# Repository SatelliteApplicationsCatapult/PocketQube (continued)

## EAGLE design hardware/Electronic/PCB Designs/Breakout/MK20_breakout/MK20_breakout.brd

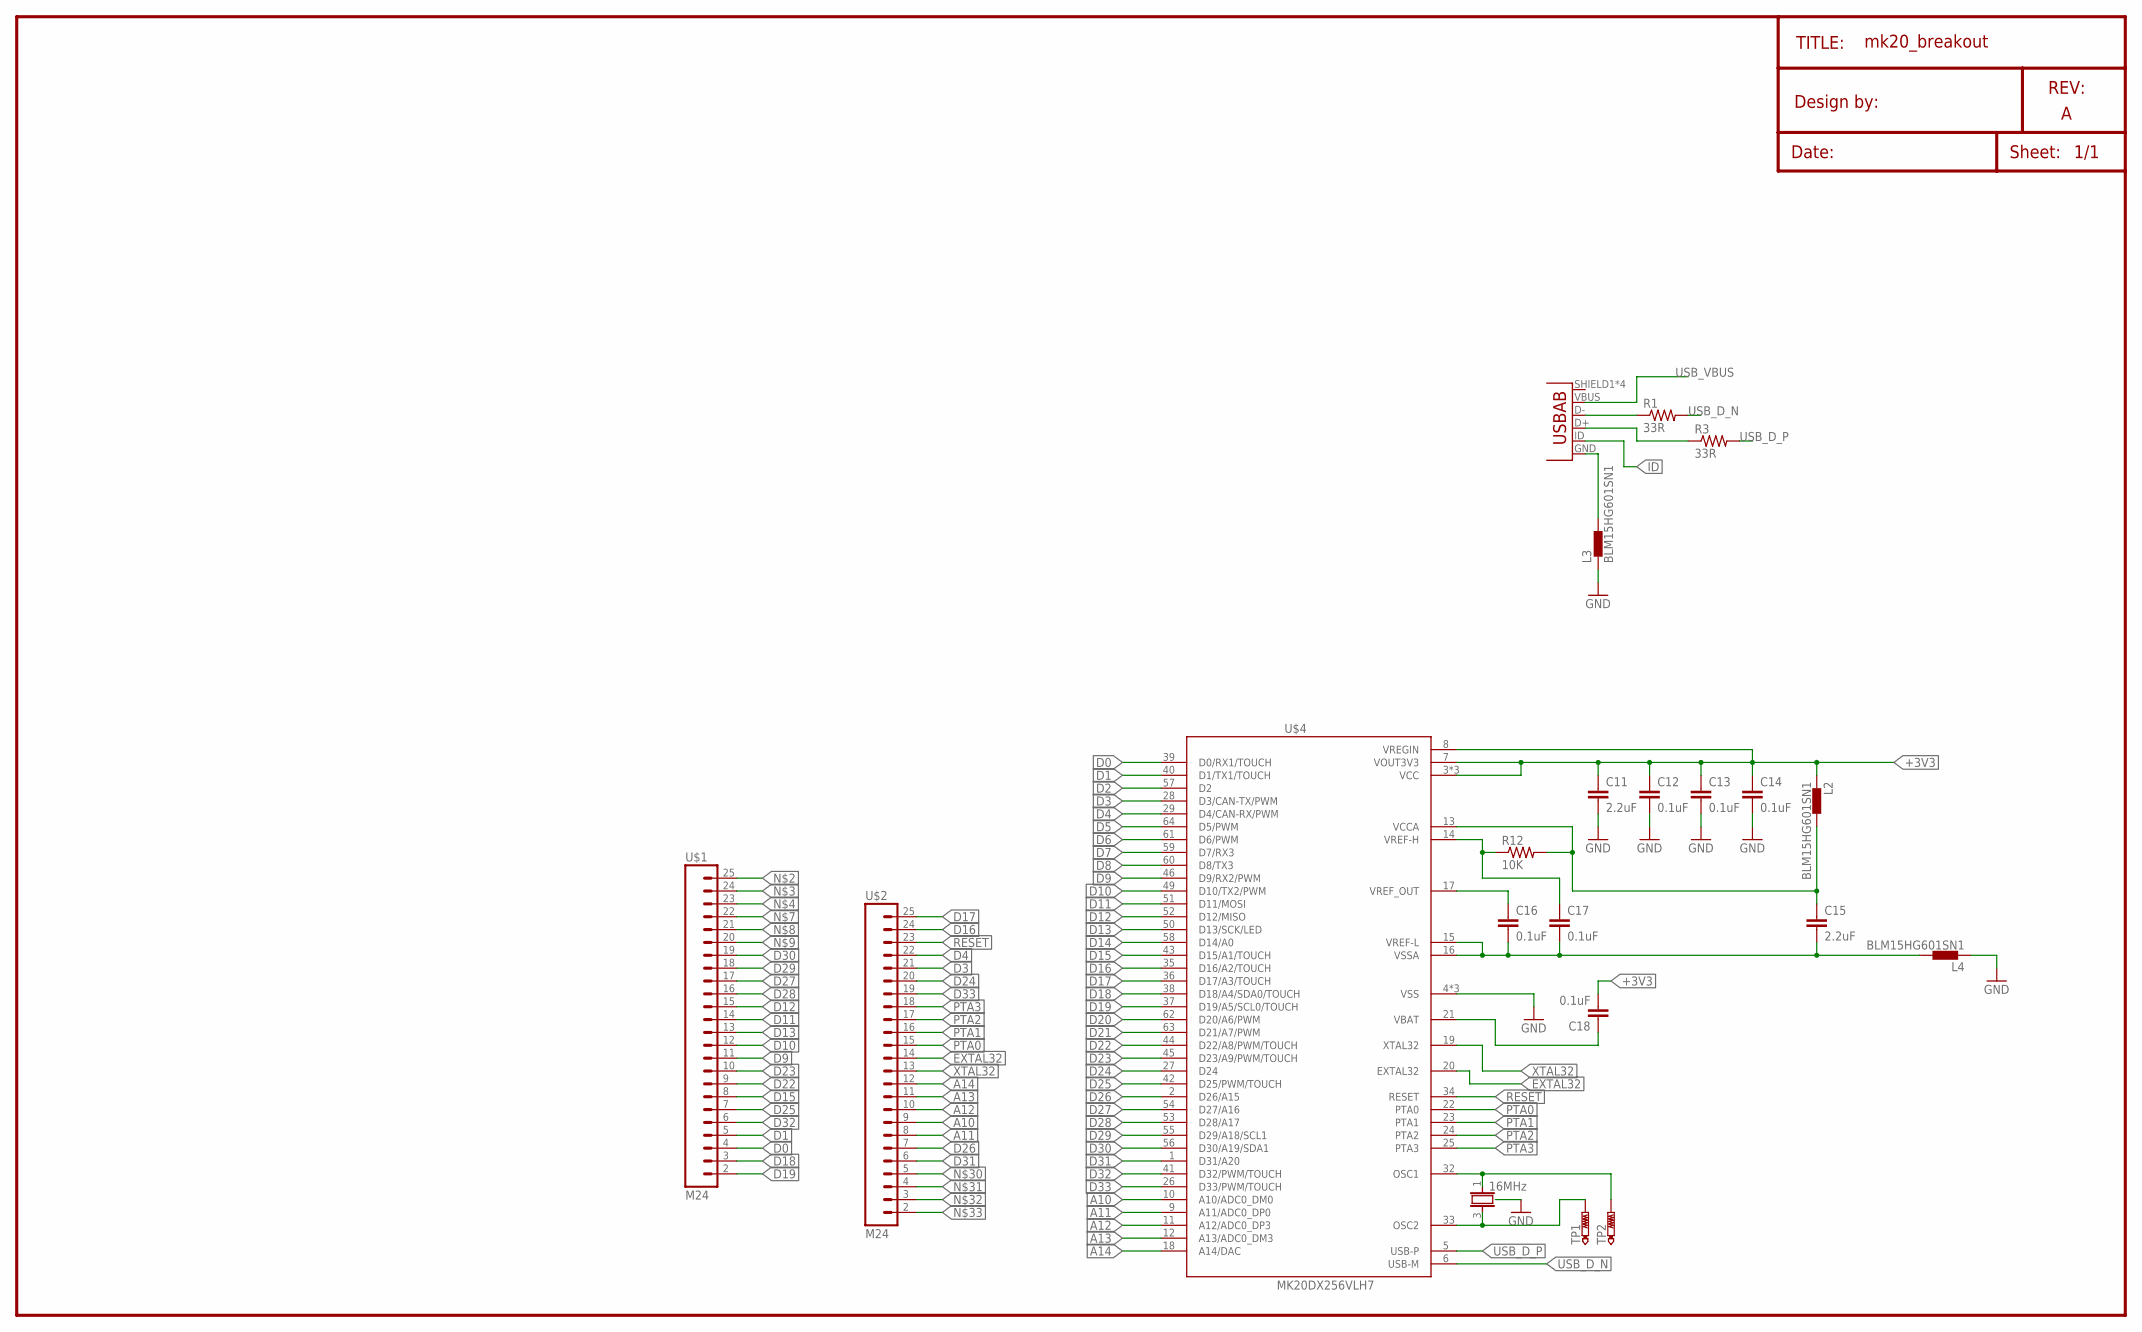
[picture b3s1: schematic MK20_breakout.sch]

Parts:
C11, C15: 2.2uF; C0603
C12, C13, C14, C16, C17: 0.1uF; C0402
C18: 0.1uF; C0603
JP1: MOLEX 105017-0001; USB-AB-MICRO-SMD
L2, L3, L4: BLM15HG601SN1; 0402
NDK_NX3225SA: 16MHz; 4SMD_DFN_LCC
R1, R3: 33R; 0603-RES
R12: 10K; 0402-RES
TP1, TP2: PTR1TP06R; TP06R
U$1, U$2: M24; 1X24
U$4: MK20DX256VLH7; QFP50P1200X1200X160-64N

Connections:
+3V3: C11.1, C12.1, C13.1, C14.1, C18.2, L2.1, U$4.3 (VCC), U$4.7 (VOUT3V3), U$4.8 (VREGIN), U$4.30 (VCC), U$4.48 (VCC)
A10: U$2.9, U$4.10 (A10/ADC0_DM0)
A11: U$2.8, U$4.9 (A11/ADC0_DP0)
A12: U$2.10, U$4.11 (A12/ADC0_DP3)
A13: U$2.11, U$4.12 (A13/ADC0_DM3)
A14: U$2.12, U$4.18 (A14/DAC)
D0: U$1.4, U$4.39 (D0/RX1/TOUCH)
D1: U$1.5, U$4.40 (D1/TX1/TOUCH)
D2: U$4.57 (D2)
D3: U$2.21, U$4.28 (D3/CAN-TX/PWM)
D4: U$2.22, U$4.29 (D4/CAN-RX/PWM)
D5: U$4.64 (D5/PWM)
D6: U$4.61 (D6/PWM)
D7: U$4.59 (D7/RX3)
D8: U$4.60 (D8/TX3)
D9: U$1.11, U$4.46 (D9/RX2/PWM)
D10: U$1.12, U$4.49 (D10/TX2/PWM)
D11: U$1.14, U$4.51 (D11/MOSI)
D12: U$1.15, U$4.52 (D12/MISO)
D13: U$1.13, U$4.50 (D13/SCK/LED)
D14: U$4.58 (D14/A0)
D15: U$1.8, U$4.43 (D15/A1/TOUCH)
D16: U$2.24, U$4.35 (D16/A2/TOUCH)
D17: U$2.25, U$4.36 (D17/A3/TOUCH)
D18: U$1.3, U$4.38 (D18/A4/SDA0/TOUCH)
D19: U$1.2, U$4.37 (D19/A5/SCL0/TOUCH)
D20: U$4.62 (D20/A6/PWM)
D21: U$4.63 (D21/A7/PWM)
D22: U$1.9, U$4.44 (D22/A8/PWM/TOUCH)
D23: U$1.10, U$4.45 (D23/A9/PWM/TOUCH)
D24: U$2.20, U$4.27 (D24)
D25: U$1.7, U$4.42 (D25/PWM/TOUCH)
D26: U$2.7, U$4.2 (D26/A15)
D27: U$1.17, U$4.54 (D27/A16)
D28: U$1.16, U$4.53 (D28/A17)
D29: U$1.18, U$4.55 (D29/A18/SCL1)
D30: U$1.19, U$4.56 (D30/A19/SDA1)
D31: U$2.6, U$4.1 (D31/A20)
D32: U$1.6, U$4.41 (D32/PWM/TOUCH)
D33: U$2.19, U$4.26 (D33/PWM/TOUCH)
EXTAL32: U$2.14, U$4.20 (EXTAL32)
GND: C11.2, C12.2, C13.2, C14.2, L3.1, L4.1, NDK_NX3225SA.GND, NDK_NX3225SA.GND@1 (GND), NDK_NX3225SA.GND@2 (GND), U$4.4 (VSS), U$4.31 (VSS), U$4.47 (VSS)
ID: JP1.ID (USBID)
unnamed: NDK_NX3225SA.1, TP2.TP, U$4.32 (OSC1)
unnamed: JP1.D+, R3.1
unnamed: JP1.D-, R1.1
unnamed: NDK_NX3225SA.3, TP1.TP, U$4.33 (OSC2)
unnamed: C15.1, L2.2, R12.2, U$4.13 (VCCA)
unnamed: C17.1, R12.1, U$4.14 (VREF-H)
unnamed: C15.2, C16.2, C17.2, L4.2, U$4.15 (VREF-L), U$4.16 (VSSA)
unnamed: C16.1, U$4.17 (VREF_OUT)
unnamed: C18.1, U$4.21 (VBAT)
unnamed: JP1.GND, L3.2
PTA0: U$2.15, U$4.22 (PTA0)
PTA1: U$2.16, U$4.23 (PTA1)
PTA2: U$2.17, U$4.24 (PTA2)
PTA3: U$2.18, U$4.25 (PTA3)
RESET: U$2.23, U$4.34 (RESET)
USB_D_N: R1.2, U$4.6 (USB-M)
USB_D_P: R3.2, U$4.5 (USB-P)
USB_VBUS: JP1.VBUS
XTAL32: U$2.13, U$4.19 (XTAL32)

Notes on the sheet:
TITLE:
Date:
REV:
Sheet:
Design by:

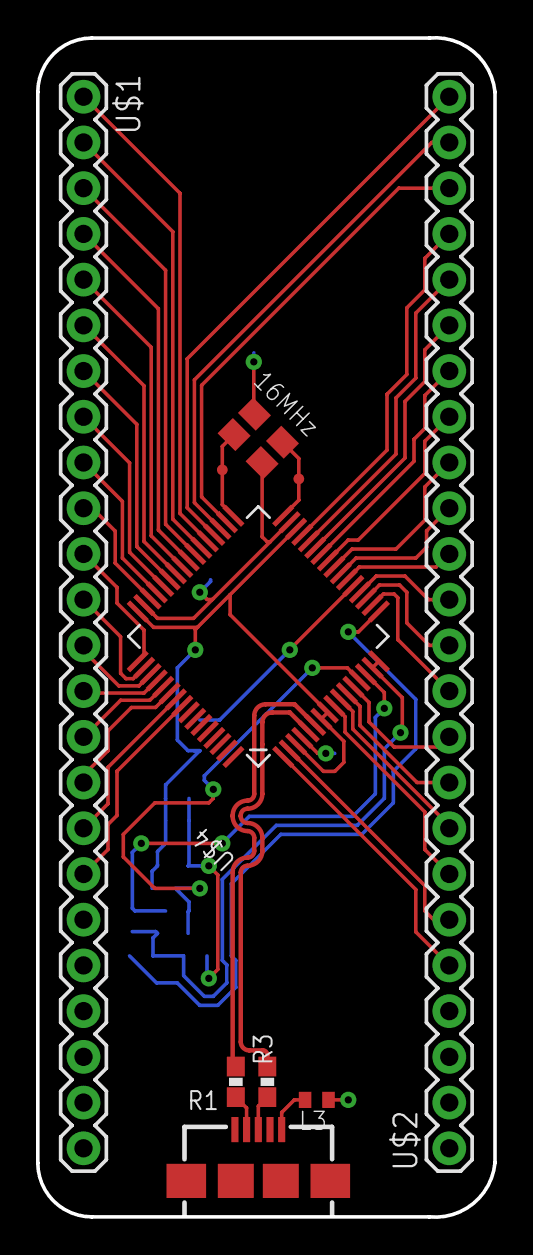
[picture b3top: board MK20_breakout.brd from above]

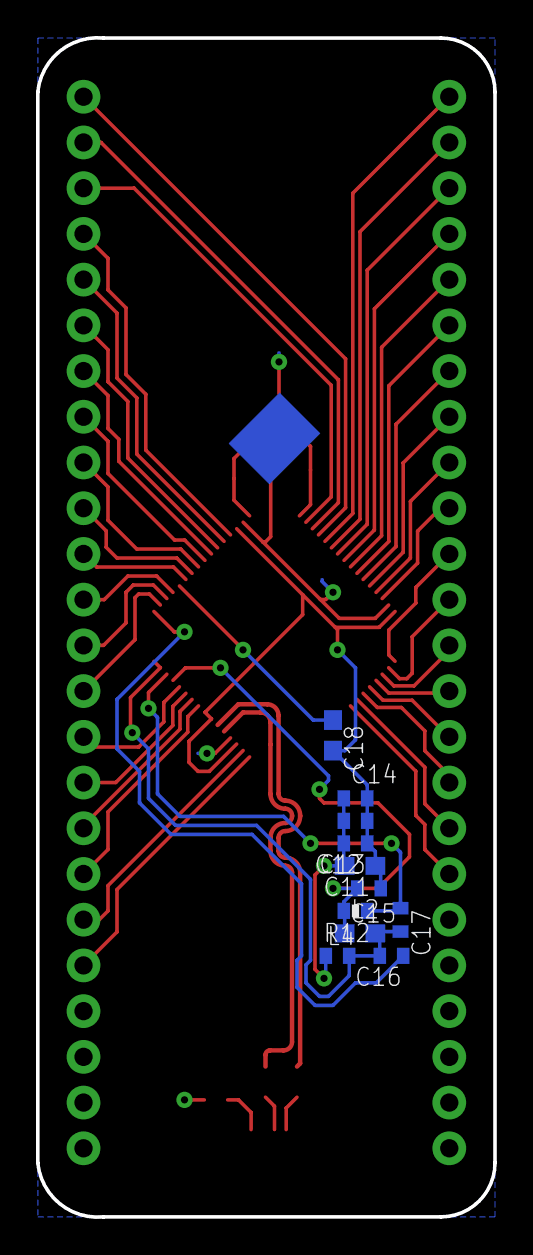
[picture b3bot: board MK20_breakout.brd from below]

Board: 2 copper layers, 25.4 x 65.5 mm, 21 parts (11 on the bottom side), 52 nets.

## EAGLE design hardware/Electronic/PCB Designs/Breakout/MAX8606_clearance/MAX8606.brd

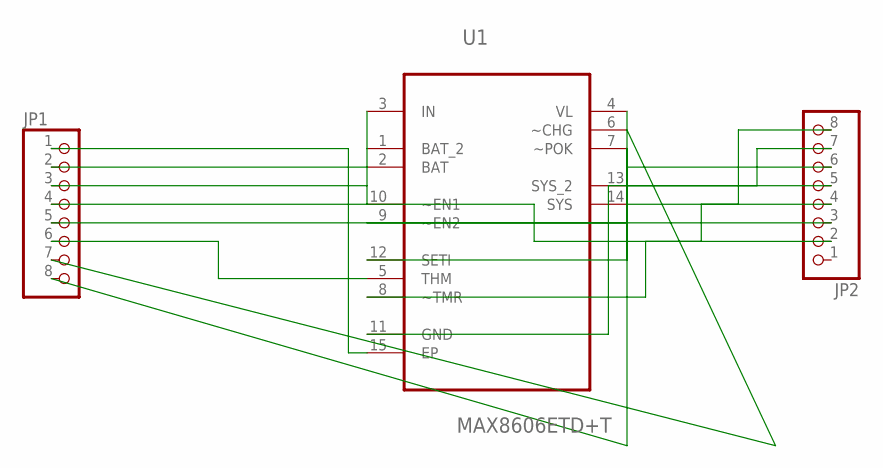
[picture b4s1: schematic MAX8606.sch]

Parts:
JP1, JP2: PINHD-1X8CLEANBIG; 1X08-CLEANBIG
U1: MAX8606ETD+T; DFN300X300X80-15N

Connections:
GND: JP1.1, JP2.5, U1.11 (GND), U1.15 (EP)
unnamed: JP2.8, U1.14 (SYS)
unnamed: JP2.7, U1.13 (SYS_2)
unnamed: JP2.6, U1.12 (SETI)
unnamed: JP2.4, U1.10 (~EN1)
unnamed: JP2.3, U1.9 (~EN2)
unnamed: JP2.2, U1.8 (~TMR)
unnamed: JP1.8, U1.7 (~POK)
unnamed: JP1.7, U1.6 (~CHG)
unnamed: JP1.5, U1.4 (VL)
unnamed: JP1.2, JP1.3, JP1.4, U1.3 (IN)
unnamed: JP1.6, U1.5 (THM)

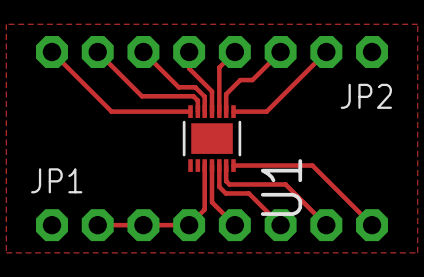
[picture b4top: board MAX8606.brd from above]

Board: 2 copper layers, 3 parts (0 on the bottom side), 12 nets.

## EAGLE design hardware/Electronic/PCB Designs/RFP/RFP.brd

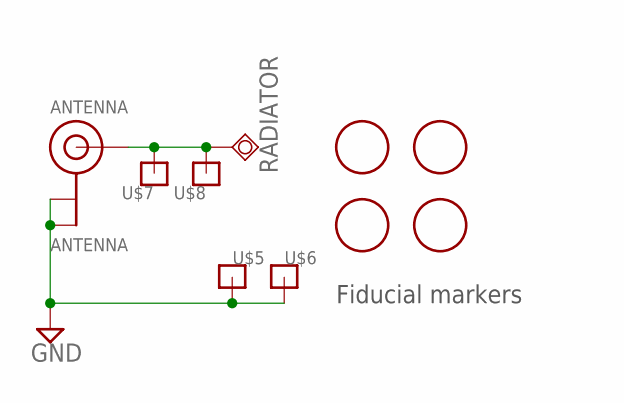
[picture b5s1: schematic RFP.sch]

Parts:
ANTENNA: ANTENNA; U.FL
FD1, FD2, FD3, FD4: FIDUCIAL; FIDUCIAL_1MM
RADIATOR: TPSQTP20SQ; TP20SQ
U$5, U$6, U$7, U$8: 2MMPILLAR

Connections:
GND: ANTENNA.1 (GND), ANTENNA.2 (GND), U$5.P$1, U$6.P$1
SIGNAL: ANTENNA.3 (SIGNAL), RADIATOR.TP, U$7.P$1, U$8.P$1

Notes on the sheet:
Fiducial markers

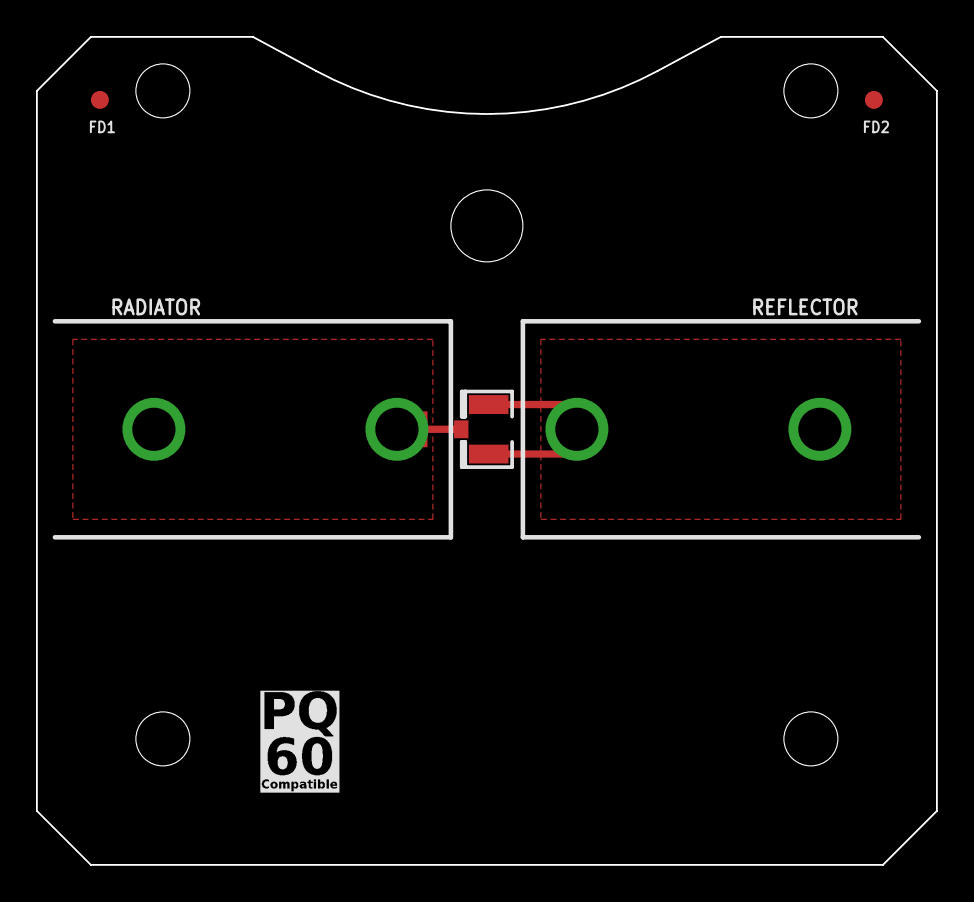
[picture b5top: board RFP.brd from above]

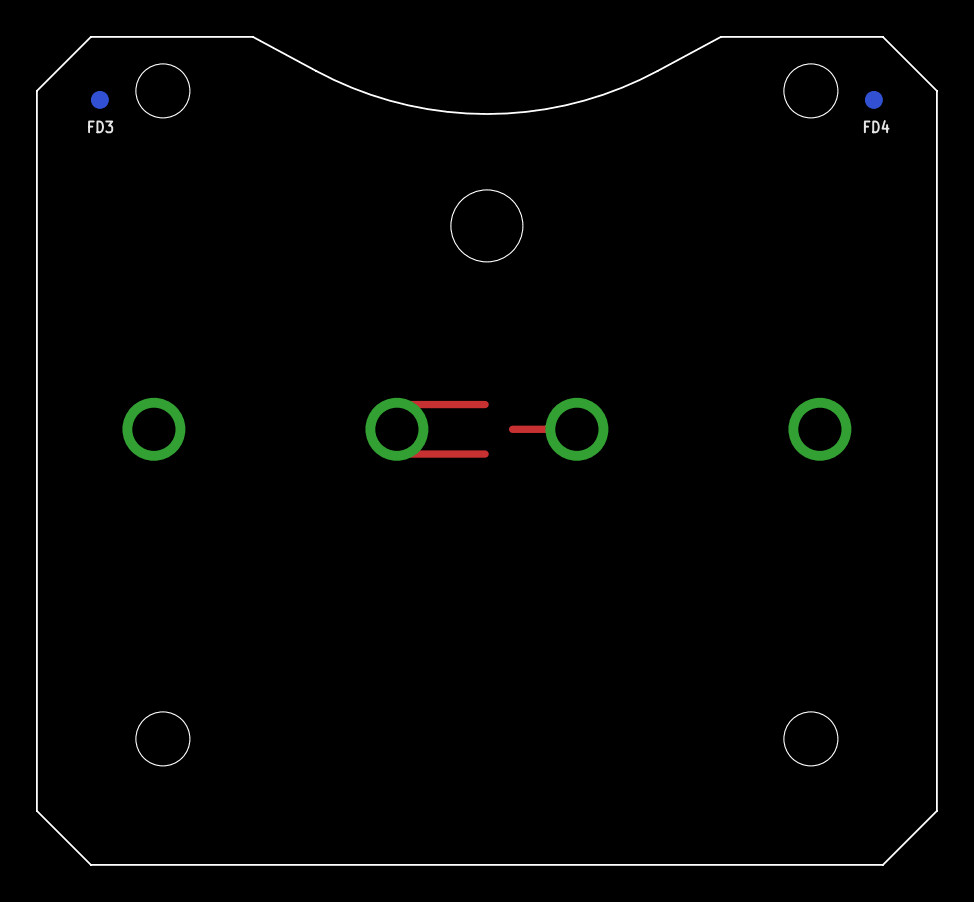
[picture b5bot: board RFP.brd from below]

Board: 2 copper layers, 50.0 x 46.0 mm, 13 parts (2 on the bottom side), 2 nets.

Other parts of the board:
U$9: SA_LOGO_SMALL
U$10: PQ60_CMP
U$12: UBO_LOGO_LARGE

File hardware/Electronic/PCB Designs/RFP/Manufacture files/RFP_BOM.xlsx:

Qty | Value | Device | Package | Parts | Description | Supplier | Order number | Notes
4 | 2MMPILLAR | 2MMPILLAR | 2MMPILLAR | U$5, U$6, U$7, U$8 |  |  |  | Do not populate
1 | ANTENNA | ANTENNA_U.FL | U.FL | ANTENNA | U.FL Antenna Connector | Farnell | 1688077 | Or compatible alternative
4 | FIDUCIAL | FIDUCIAL | FIDUCIAL_1MM | FD1, FD2, FD3, FD4 | For use by pick and place machines to calibrate the vision/machine, 1mm |  |  | Do not populate
1 | TPSQTP20SQ | TPSQTP20SQ | TP20SQ | RADIATOR | Test pad |  |  | Do not populate

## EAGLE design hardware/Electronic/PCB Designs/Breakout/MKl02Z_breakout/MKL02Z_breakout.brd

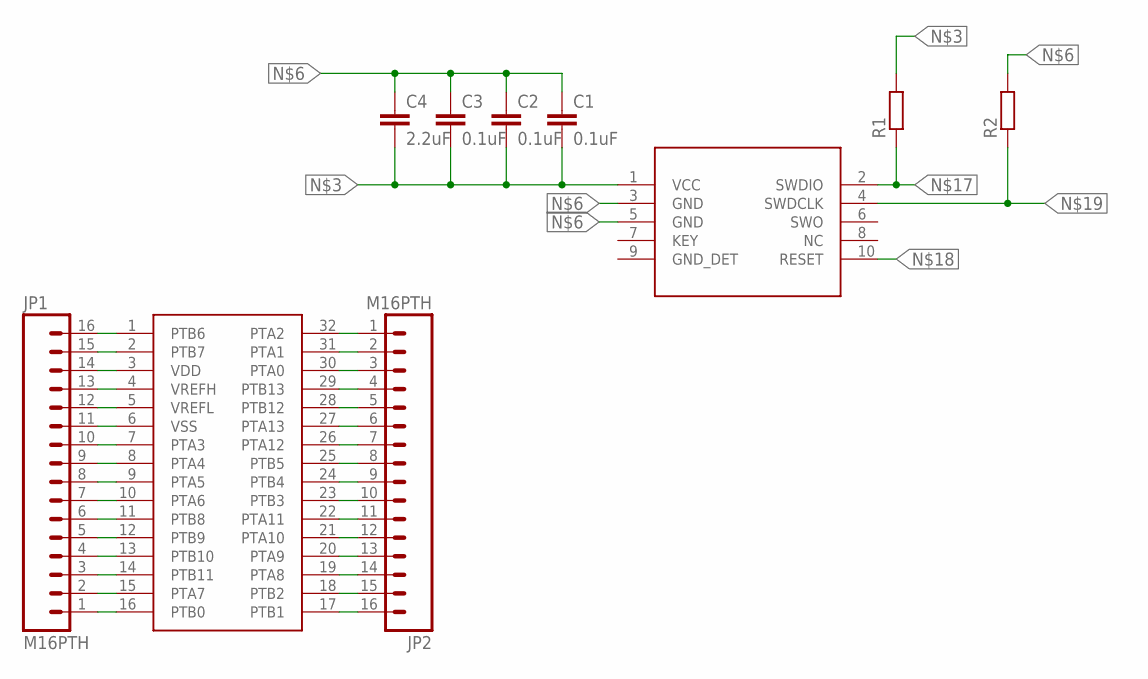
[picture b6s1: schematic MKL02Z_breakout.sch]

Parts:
C1, C2, C3: 0.1uF; C0603
C4: 2.2uF; C0603
JP1, JP2: M16PTH; 1X16
R1, R2: R-EU_R0603; R0603
U$1: MKL02Z16VFM4
U$2: SWD_10_PIN

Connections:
unnamed: JP1.16, U$1.1 (PTB6)
unnamed: JP1.15, U$1.2 (PTB7)
unnamed: C1.2, C2.2, C3.2, C4.2, JP1.14, R1.2, U$1.3 (VDD), U$2.1 (VCC)
unnamed: JP1.13, U$1.4 (VREFH)
unnamed: JP1.12, U$1.5 (VREFL)
unnamed: C1.1, C2.1, C3.1, C4.1, JP1.11, R2.2, U$1.6 (VSS), U$2.3 (GND), U$2.5 (GND)
unnamed: JP1.10, U$1.7 (PTA3)
unnamed: JP1.9, U$1.8 (PTA4)
unnamed: JP1.8, U$1.9 (PTA5)
unnamed: JP1.7, U$1.10 (PTA6)
unnamed: JP1.6, U$1.11 (PTB8)
unnamed: JP1.5, U$1.12 (PTB9)
unnamed: JP1.4, U$1.13 (PTB10)
unnamed: JP1.3, U$1.14 (PTB11)
unnamed: JP1.2, U$1.15 (PTA7)
unnamed: JP1.1, U$1.16 (PTB0)
unnamed: JP2.1, R1.1, U$1.32 (PTA2), U$2.2 (SWDIO)
unnamed: JP2.2, U$1.31 (PTA1), U$2.10 (RESET)
unnamed: JP2.3, R2.1, U$1.30 (PTA0), U$2.4 (SWDCLK)
unnamed: JP2.4, U$1.29 (PTB13)
unnamed: JP2.5, U$1.28 (PTB12)
unnamed: JP2.6, U$1.27 (PTA13)
unnamed: JP2.7, U$1.26 (PTA12)
unnamed: JP2.8, U$1.25 (PTB5)
unnamed: JP2.9, U$1.24 (PTB4)
unnamed: JP2.10, U$1.23 (PTB3)
unnamed: JP2.11, U$1.22 (PTA11)
unnamed: JP2.12, U$1.21 (PTA10)
unnamed: JP2.13, U$1.20 (PTA9)
unnamed: JP2.14, U$1.19 (PTA8)
unnamed: JP2.15, U$1.18 (PTB2)
unnamed: JP2.16, U$1.17 (PTB1)

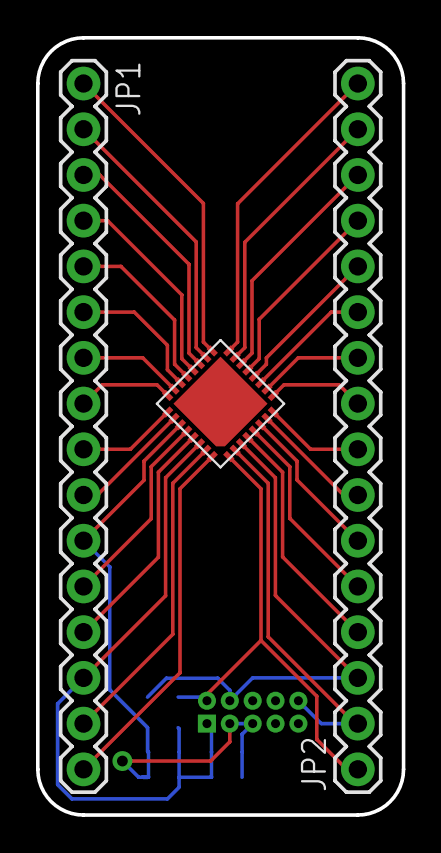
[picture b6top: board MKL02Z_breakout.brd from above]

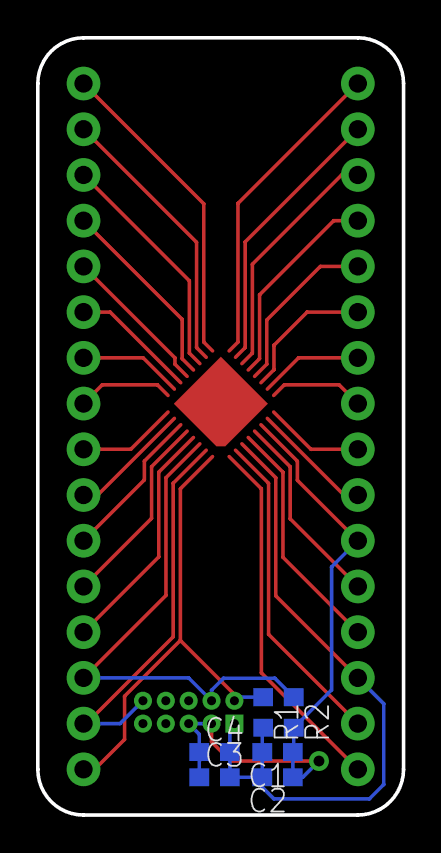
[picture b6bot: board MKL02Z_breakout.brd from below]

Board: 2 copper layers, 20.3 x 43.2 mm, 10 parts (6 on the bottom side), 32 nets.

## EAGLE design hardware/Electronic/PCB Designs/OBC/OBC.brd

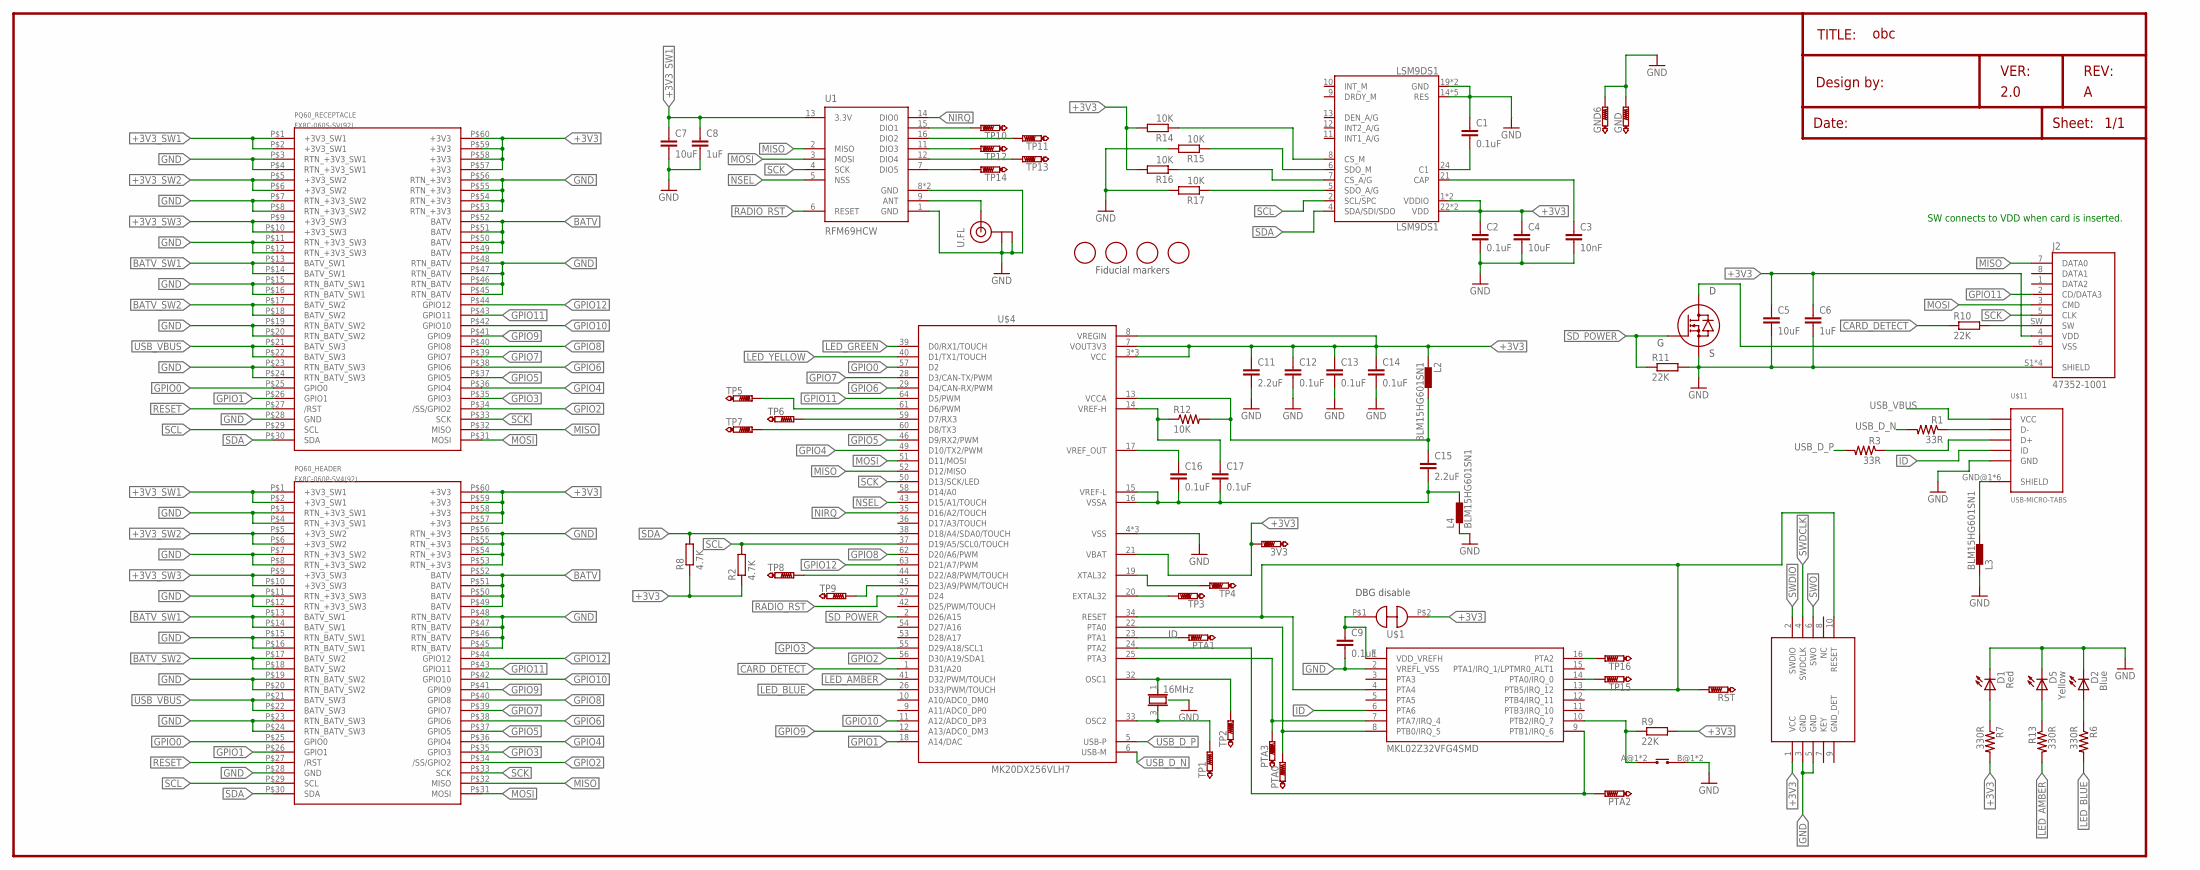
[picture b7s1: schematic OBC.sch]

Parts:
3V3: PTR1TP06R; TP06R
C1, C2, C9, C12, C13, C14, C16, C17: 0.1uF; C0402
C3: 10nF; C0402
C4, C5, C7: 10uF; C0805
C6, C8: 1uF; C0603
C11, C15: 2.2uF; C0603
D1: Red; CHIPLED_0603
D2: Blue; CHIPLED_0603
D5: Yellow; CHIPLED_0603
ERASE: EVPAF7B70
FD1, FD2, FD3, FD4: FIDUCIAL; FIDUCIAL_1MM
GND, GND6: PTR1TP06R; TP06R
J2: 47352-1001; MOLEX_47352-1001
L2, L3, L4: BLM15HG601SN1; 0402
LSM9DS1: LSM9DS1; LGA24-8X4
NDK_NX3225SA: 16MHz; 4SMD_DFN_LCC
PQ60_HEADER: FX8C-060P-SV4(92)
PQ60_RECEPTACLE: FX8C-060S-SV(92)
PTA0, PTA1, PTA2, PTA3: PTR1TP06R; TP06R
R1, R3: 33R; 0603-RES
R2, R8: 4.7K; R0402
R6, R7, R13: 330R; 0603-RES
R9, R10, R11: 22K; R0402
R12: 10K; 0402-RES
R14, R15, R16, R17: 10K; R0402
RST: PTR1TP06R; TP06R
SJ3: SJNC
TP1, TP2, TP3, TP4, TP5, TP6, TP7, TP8, TP9, TP10, TP11, TP12, TP13, TP14, TP15, TP16: PTR1TP06R; TP06R
U1: RFM69HCW; RFM69HCW-XXXS2
U$1: MKL02Z32VFG4SMD; QFN16
U$3: PMV40UN2; SOT23-3
U$4: MK20DX256VLH7; QFP50P1200X1200X160-64N
U$9: SWD_10_PIN
U$11: USB-MICRO-TABS
U.FL: U.FL

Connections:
+3V3: 3V3.TP, C2.1, C4.1, C5.1, C6.1, C11.1, C12.1, C13.1, C14.1, J2.4 (VDD), L2.1, LSM9DS1.1 (VDDIO), LSM9DS1.3 (VDDIO), LSM9DS1.22 (VDD), LSM9DS1.23 (VDD), PQ60_HEADER.P$57 (+3V3), PQ60_HEADER.P$58 (+3V3), PQ60_HEADER.P$59 (+3V3), PQ60_HEADER.P$60 (+3V3), PQ60_RECEPTACLE.P$57 (+3V3), PQ60_RECEPTACLE.P$58 (+3V3), PQ60_RECEPTACLE.P$59 (+3V3), PQ60_RECEPTACLE.P$60 (+3V3), R2.1, R7.2, R8.1, R9.2, R14.2, R16.2, SJ3.P$2, U$4.3 (VCC), U$4.7 (VOUT3V3), U$4.8 (VREGIN), U$4.21 (VBAT), U$4.30 (VCC), U$4.48 (VCC), U$9.1 (VCC)
+3V3_SW1: C7.1, C8.1, PQ60_HEADER.P$1 (+3V3_SW1), PQ60_HEADER.P$2 (+3V3_SW1), PQ60_RECEPTACLE.P$1 (+3V3_SW1), PQ60_RECEPTACLE.P$2 (+3V3_SW1), U1.13 (3.3V)
+3V3_SW2: PQ60_HEADER.P$5 (+3V3_SW2), PQ60_HEADER.P$6 (+3V3_SW2), PQ60_RECEPTACLE.P$5 (+3V3_SW2), PQ60_RECEPTACLE.P$6 (+3V3_SW2)
+3V3_SW3: PQ60_HEADER.P$9 (+3V3_SW3), PQ60_HEADER.P$10 (+3V3_SW3), PQ60_RECEPTACLE.P$9 (+3V3_SW3), PQ60_RECEPTACLE.P$10 (+3V3_SW3)
BATV: PQ60_HEADER.P$49 (BATV), PQ60_HEADER.P$50 (BATV), PQ60_HEADER.P$51 (BATV), PQ60_HEADER.P$52 (BATV), PQ60_RECEPTACLE.P$49 (BATV), PQ60_RECEPTACLE.P$50 (BATV), PQ60_RECEPTACLE.P$51 (BATV), PQ60_RECEPTACLE.P$52 (BATV)
BATV_SW1: PQ60_HEADER.P$13 (BATV_SW1), PQ60_HEADER.P$14 (BATV_SW1), PQ60_RECEPTACLE.P$13 (BATV_SW1), PQ60_RECEPTACLE.P$14 (BATV_SW1)
BATV_SW2: PQ60_HEADER.P$17 (BATV_SW2), PQ60_HEADER.P$18 (BATV_SW2), PQ60_RECEPTACLE.P$17 (BATV_SW2), PQ60_RECEPTACLE.P$18 (BATV_SW2)
CARD_DETECT: R10.1, U$4.1 (D31/A20)
GND: C1.1, C2.2, C3.2, C4.2, C5.2, C6.2, C7.2, C8.2, C9.2, C11.2, C12.2, C13.2, C14.2, D1.C, D2.C, D5.C, ERASE.B@1, ERASE.B@2, GND.TP, GND6.TP, J2.S1 (SHIELD), J2.S2 (SHIELD), J2.S3 (SHIELD), J2.S4 (SHIELD), L3.1, L4.1, LSM9DS1.14 (RES), LSM9DS1.15 (RES), LSM9DS1.16 (RES), LSM9DS1.17 (RES), LSM9DS1.18 (RES), LSM9DS1.19 (GND), LSM9DS1.20 (GND), NDK_NX3225SA.GND, NDK_NX3225SA.GND@1 (GND), NDK_NX3225SA.GND@2 (GND), PQ60_HEADER.P$3 (RTN_+3V3_SW1), PQ60_HEADER.P$4 (RTN_+3V3_SW1), PQ60_HEADER.P$7 (RTN_+3V3_SW2), PQ60_HEADER.P$8 (RTN_+3V3_SW2), PQ60_HEADER.P$11 (RTN_+3V3_SW3), PQ60_HEADER.P$12 (RTN_+3V3_SW3), PQ60_HEADER.P$15 (RTN_BATV_SW1), PQ60_HEADER.P$16 (RTN_BATV_SW1), PQ60_HEADER.P$19 (RTN_BATV_SW2), PQ60_HEADER.P$20 (RTN_BATV_SW2), PQ60_HEADER.P$23 (RTN_BATV_SW3), PQ60_HEADER.P$24 (RTN_BATV_SW3), PQ60_HEADER.P$28 (GND), PQ60_HEADER.P$45 (RTN_BATV), PQ60_HEADER.P$46 (RTN_BATV), PQ60_HEADER.P$47 (RTN_BATV), PQ60_HEADER.P$48 (RTN_BATV), PQ60_HEADER.P$53 (RTN_+3V3), PQ60_HEADER.P$54 (RTN_+3V3), PQ60_HEADER.P$55 (RTN_+3V3), PQ60_HEADER.P$56 (RTN_+3V3), PQ60_RECEPTACLE.P$3 (RTN_+3V3_SW1), PQ60_RECEPTACLE.P$4 (RTN_+3V3_SW1), PQ60_RECEPTACLE.P$7 (RTN_+3V3_SW2), PQ60_RECEPTACLE.P$8 (RTN_+3V3_SW2), PQ60_RECEPTACLE.P$11 (RTN_+3V3_SW3), PQ60_RECEPTACLE.P$12 (RTN_+3V3_SW3), PQ60_RECEPTACLE.P$15 (RTN_BATV_SW1), PQ60_RECEPTACLE.P$16 (RTN_BATV_SW1), PQ60_RECEPTACLE.P$19 (RTN_BATV_SW2), PQ60_RECEPTACLE.P$20 (RTN_BATV_SW2), PQ60_RECEPTACLE.P$23 (RTN_BATV_SW3), PQ60_RECEPTACLE.P$24 (RTN_BATV_SW3), PQ60_RECEPTACLE.P$28 (GND), PQ60_RECEPTACLE.P$45 (RTN_BATV), PQ60_RECEPTACLE.P$46 (RTN_BATV), PQ60_RECEPTACLE.P$47 (RTN_BATV), PQ60_RECEPTACLE.P$48 (RTN_BATV), PQ60_RECEPTACLE.P$53 (RTN_+3V3), PQ60_RECEPTACLE.P$54 (RTN_+3V3), PQ60_RECEPTACLE.P$55 (RTN_+3V3), PQ60_RECEPTACLE.P$56 (RTN_+3V3), R11.2, R15.2, R17.2, U1.1 (GND), U1.8 (GND), U1.10 (GND), U$1.2 (VREFL_VSS), U$3.2 (S), U$4.4 (VSS), U$4.31 (VSS), U$4.47 (VSS), U$9.3 (GND), U$9.5 (GND), U$11.PIN$5 (GND), U.FL.P$1 (GND), U.FL.P$2 (GND)
GPIO0: PQ60_HEADER.P$25 (GPIO0), PQ60_RECEPTACLE.P$25 (GPIO0), U$4.57 (D2)
GPIO1: PQ60_HEADER.P$26 (GPIO1), PQ60_RECEPTACLE.P$26 (GPIO1), U$4.18 (A14/DAC)
GPIO2: PQ60_HEADER.P$34 (/SS/GPIO2), PQ60_RECEPTACLE.P$34 (/SS/GPIO2), U$4.56 (D30/A19/SDA1)
GPIO3: PQ60_HEADER.P$35 (GPIO3), PQ60_RECEPTACLE.P$35 (GPIO3), U$4.55 (D29/A18/SCL1)
GPIO4: PQ60_HEADER.P$36 (GPIO4), PQ60_RECEPTACLE.P$36 (GPIO4), U$4.49 (D10/TX2/PWM)
GPIO5: PQ60_HEADER.P$37 (GPIO5), PQ60_RECEPTACLE.P$37 (GPIO5), U$4.46 (D9/RX2/PWM)
GPIO6: PQ60_HEADER.P$38 (GPIO6), PQ60_RECEPTACLE.P$38 (GPIO6), U$4.29 (D4/CAN-RX/PWM)
GPIO7: PQ60_HEADER.P$39 (GPIO7), PQ60_RECEPTACLE.P$39 (GPIO7), U$4.28 (D3/CAN-TX/PWM)
GPIO8: PQ60_HEADER.P$40 (GPIO8), PQ60_RECEPTACLE.P$40 (GPIO8), U$4.62 (D20/A6/PWM)
GPIO9: PQ60_HEADER.P$41 (GPIO9), PQ60_RECEPTACLE.P$41 (GPIO9), U$4.12 (A13/ADC0_DM3)
GPIO10: PQ60_HEADER.P$42 (GPIO10), PQ60_RECEPTACLE.P$42 (GPIO10), U$4.11 (A12/ADC0_DP3)
GPIO11: J2.2 (CD/DATA3), PQ60_HEADER.P$43 (GPIO11), PQ60_RECEPTACLE.P$43 (GPIO11), U$4.64 (D5/PWM)
GPIO12: PQ60_HEADER.P$44 (GPIO12), PQ60_RECEPTACLE.P$44 (GPIO12), U$4.63 (D21/A7/PWM)
ID: PTA1.TP, U$1.6 (PTA6), U$4.23 (PTA1), U$11.P$4 (ID)
LED_AMBER: R13.2, U$4.41 (D32/PWM/TOUCH)
LED_BLUE: R6.2, U$4.26 (D33/PWM/TOUCH)
LED_GREEN: U$4.39 (D0/RX1/TOUCH)
LED_YELLOW: U$4.40 (D1/TX1/TOUCH)
MISO: J2.7 (DATA0), PQ60_HEADER.P$32 (MISO), PQ60_RECEPTACLE.P$32 (MISO), U1.2 (MISO), U$4.52 (D12/MISO)
MOSI: J2.3 (CMD), PQ60_HEADER.P$31 (MOSI), PQ60_RECEPTACLE.P$31 (MOSI), U1.3 (MOSI), U$4.51 (D11/MOSI)
unnamed: NDK_NX3225SA.1, TP2.TP, U$4.32 (OSC1)
unnamed: C9.1, SJ3.P$1, U$1.1 (VDD_VREFH)
unnamed: ERASE.A@1, ERASE.A@2, R9.1, U$1.10 (PTB2/IRQ_7)
unnamed: TP4.TP, U$4.19 (XTAL32)
unnamed: R3.1, U$11.P$3 (D+)
unnamed: R1.1, U$11.P$2 (D-)
unnamed: TP3.TP, U$4.20 (EXTAL32)
unnamed: TP5.TP, U$4.61 (D6/PWM)
unnamed: J2.SW, R10.2
unnamed: TP16.TP, U$1.16 (PTA2)
unnamed: TP10.TP, U1.15 (DIO1)
unnamed: U1.9 (ANT), U.FL.P$3 (SIGNAL)
unnamed: TP11.TP, U1.16 (DIO2)
unnamed: J2.6 (VSS), U$3.3 (D)
unnamed: TP12.TP, U1.11 (DIO3)
unnamed: D2.A, R6.1
unnamed: TP13.TP, U1.12 (DIO4)
unnamed: TP14.TP, U1.7 (DIO5)
unnamed: RST.TP, U$1.4 (PTA4), U$1.13 (PTB5/IRQ_12), U$4.34 (RESET), U$9.10 (RESET)
unnamed: TP15.TP, U$1.14 (PTA0/IRQ_0)
unnamed: D1.A, R7.1
unnamed: NDK_NX3225SA.3, TP1.TP, U$4.33 (OSC2)
unnamed: C15.1, L2.2, R12.2, U$4.13 (VCCA)
unnamed: C17.1, R12.1, U$4.14 (VREF-H)
unnamed: C15.2, C16.2, C17.2, L4.2, U$4.15 (VREF-L), U$4.16 (VSSA)
unnamed: C16.1, U$4.17 (VREF_OUT)
unnamed: TP6.TP, U$4.59 (D7/RX3)
unnamed: TP7.TP, U$4.60 (D8/TX3)
unnamed: TP8.TP, U$4.44 (D22/A8/PWM/TOUCH)
unnamed: TP9.TP, U$4.45 (D23/A9/PWM/TOUCH)
unnamed: C1.2, LSM9DS1.24 (C1)
unnamed: C3.1, LSM9DS1.21 (CAP)
unnamed: LSM9DS1.7 (CS_A/G), R16.1
unnamed: LSM9DS1.8 (CS_M), R14.1
unnamed: D5.A, R13.1
unnamed: LSM9DS1.6 (SDO_M), R15.1
unnamed: LSM9DS1.5 (SDO_A/G), R17.1
NIRQ: U1.14 (DIO0), U$4.35 (D16/A2/TOUCH)
NSEL: U1.5 (NSS), U$4.43 (D15/A1/TOUCH)
RADIO_RST: U1.6 (RESET), U$4.27 (D24)
RESET: PQ60_HEADER.P$27 (/RST), PQ60_RECEPTACLE.P$27 (/RST)
SCK: J2.5 (CLK), PQ60_HEADER.P$33 (SCK), PQ60_RECEPTACLE.P$33 (SCK), U1.4 (SCK), U$4.50 (D13/SCK/LED)
SCL: LSM9DS1.2 (SCL/SPC), PQ60_HEADER.P$29 (SCL), PQ60_RECEPTACLE.P$29 (SCL), R2.2, U$4.37 (D19/A5/SCL0/TOUCH)
SDA: LSM9DS1.4 (SDA/SDI/SDO), PQ60_HEADER.P$30 (SDA), PQ60_RECEPTACLE.P$30 (SDA), R8.2, U$4.38 (D18/A4/SDA0/TOUCH)
SD_POWER: R11.1, U$3.1 (G), U$4.2 (D26/A15)
SHIELD: L3.2, U$11.GND@1 (SHIELD), U$11.GND@2 (SHIELD), U$11.GND@3 (SHIELD), U$11.GND@4 (SHIELD), U$11.GND@5 (SHIELD), U$11.GND@6 (SHIELD)
SWDCLK: PTA0.TP, U$1.8 (PTB0/IRQ_5), U$4.22 (PTA0), U$9.4 (SWDCLK)
SWDIO: PTA3.TP, U$1.7 (PTA7/IRQ_4), U$4.25 (PTA3), U$9.2 (SWDIO)
SWO: PTA2.TP, U$1.9 (PTB1/IRQ_6), U$4.24 (PTA2), U$9.6 (SWO)
USB_D_N: R1.2, U$4.6 (USB-M)
USB_D_P: R3.2, U$4.5 (USB-P)
USB_VBUS: PQ60_HEADER.P$21 (BATV_SW3), PQ60_HEADER.P$22 (BATV_SW3), PQ60_RECEPTACLE.P$21 (BATV_SW3), PQ60_RECEPTACLE.P$22 (BATV_SW3), U$11.P$1 (VCC)

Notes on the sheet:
TITLE:
Date:
VER:
2.0
Sheet:
Design by:
REV:
Fiducial markers
DBG disable
SW connects to VDD when card is inserted.
